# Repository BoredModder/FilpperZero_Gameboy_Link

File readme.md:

# Flipper Zero: Gameboy Link Port Module

This is a module I worked on as a project to learn about PCB design, but to also learn about KiCAD, which is the program that was used to create this. I used [GAME BOY Pokemon Trading MALVEKE](https://github.com/EstebanFuentealba/Flipper-Zero-Game-Boy-Pokemon-Trading) to create this. Check is out because he is a way smarter guy than I.

If you want a simple way to get the PCB it is up in [OshPark](https://oshpark.com/shared_projects/AM6fH1JK).

I use his GPIO layout so you will want to do the same on your flipper zero. If you use his Pokemon app in [flipper.net](https://lab.flipper.net/apps/pokemon) then it will be the under "Select Pinout" > "Original".

Copied shamelessly off of his Github.

| Cable Game Link (Socket) | Flipper Zero GPIO 
| ----------- | -----------
| 6 (GND) | 8 (GND)
| 5 (CLK) | 6 (B2)
| 3 (SI) | 7 (C3)
| 2 (SO) | 5 (B3)

## Bill of Materials (BOM)

| Symbol | Material | Link
| ----------- | ----------- | ----------- |
| R1 | Resistor - 3.3k OHM 1% 1/10W 0603 SMD | [Link](https://www.digikey.com/en/products/detail/stackpole-electronics-inc/RMCF0603FT3K30/1761032) (Digikey)
| R2 | Resistor - 150 OHM 1% 1/10W 0603 SMD | [Link](https://www.digikey.com/en/products/detail/walsin-technology-corporation/WR06X1500FTL/13239274) (Digikey)
| D1 | LED - Clear Red 2.2V 0603 SMD| [Link](https://www.digikey.com/en/products/detail/inolux/IN-S63ATR/7604934) (Digikey)
| J1 | 4 Pin Connector Header | [Link](https://www.digikey.com/en/products/detail/w%C3%BCrth-elektronik/61300411121/4846827) (Digikey)
| N/A | Gameboy Link Port | [Link](https://www.aliexpress.com/i/3256803930669143.html?gatewayAdapt=4itemAdapt) (AliExpress)

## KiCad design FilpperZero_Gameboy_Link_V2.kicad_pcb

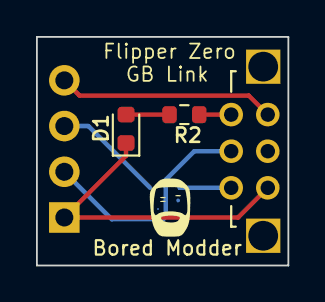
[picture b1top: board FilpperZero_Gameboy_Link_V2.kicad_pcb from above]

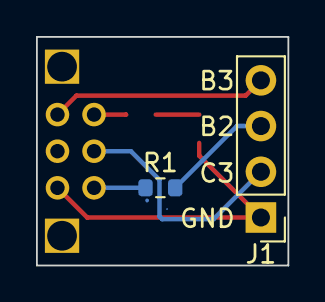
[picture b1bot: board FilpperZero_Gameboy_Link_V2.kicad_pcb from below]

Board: 2 copper layers, 14.0 x 12.7 mm, 5 parts (2 on the bottom side), 7 nets.

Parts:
D1: LED; LED_0603_1608Metric
J1: 0022232041; PinHeader_1x04_P2.54mm_Vertical
P1: LINKPORTCGB-LINK; CGB-LINK
R1: 33k; R_0603_1608Metric
R2: 150; R_0603_1608Metric

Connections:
GND: D1.1 (K), J1.1, P1.GND
unnamed: D1.2 (A), R2.2
unnamed: J1.2, P1.IN
unnamed: J1.3, R1.1
unnamed: J1.4, P1.OUT
unnamed: P1.+5V, R2.1
unnamed: P1.CLK, R1.2

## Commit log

2024-02-27 Cleaned up the folder
    Tried to tidy up for other user to follow more easily
2024-02-27 Created a readme
    Created a quick readme to help other users understand the module.
2024-02-27 readme fix
    Fixed an issue with forward and back slashes on the image link
2024-02-27 Update readme.md
    Added a bit more info and corrections
2024-02-27 Update readme.md
    Updated BOM
2024-02-27 update ignore
    Corrected the ignore
2024-02-27 Removed backups
